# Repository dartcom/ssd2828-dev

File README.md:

# SSD2828-DEV
A collection of boards to test the SSD2828 RGB to MIPI Converter with the LH154Q01 panel by AUO and the VS035ZSM by BOE. The boards are meant to be ordered as a single unit and then be separated using a box cutter ( the dust generated by cutting cutting FR4 is carcenogenic PLEASE be carefull! ).

<br></br>

# The pcb
The pcb is designed using the JLC04161H-7628 stackup by JLCPCB.  The MIPI DSI protool requires controlled impedance traces to function properly (100Ω differental, 50Ω single ended), depending on the provided pcb stackup different trace widths and spacings need to be selected. Additionally the signals must be kept away from noise sources such as inductors and other signals. When switching layers with MIPI signals, GND vias need to be placed near the signal vias.

# LH154Q01 panel
The LH154Q01 panel has been tested and is working correctly.

The panel does not support packed pixel stream packets, the only way to send pixel data to the display, is through DCS commands. in this demo, a STM32f401 is sending the the write_memory_continue(0x3C) DCS command containing pixel data, through SPI to the SSD2828. 

<br></br>

# VS035ZSM panel
The VS035ZSM panel has been tested and is working correctly.

The panel gets initialized on MIPI LP mode and the video is transmitted MIPI HS mode @912Mbps per lane. The ssd2828 is generating the test video signal called BIST. The panel has 8-bit color depth, reaning each pixel requires 24bits. The resolution of the panel is 1400x1600, including the porch values the total resoution is 1470 x 167. To operate at 60fps, 1470 x 1670 x 24 x 60 = 3.53Gbps are required resulting at 883Mbps per lane. The panel also suppors VESA DSC making 90fps operation possible. Unfortunately the SSD2828 does not include a DSC encoder. 

<br></br>

# Resources
### PCB
- [jlcpcb capabilities](https://jlcpcb.com/capabilities/pcb-capabilities).
- [jlcpcb impedance calculator](https://jlcpcb.com/pcb-impedance-calculator).
- [Jacinto 7 High-Speed Interface Layout Guidelines](https://www.ti.com/lit/an/spracp4/spracp4.pdf?ts=1708080453311&ref_url=https%253A%252F%252Fwww.google.com%252F).
- [MIPI DSI guidelines]( https://electronics.stackexchange.com/questions/610671/mipi-dsi-differential-pair-layout-guidance).
- [High-Speed PCB Design Tips - Phil's Lab](https://www.youtube.com/watch?v=VRJI0X-6yTg).
- [Differential Pairs - PCB Design Basics - Phil's Lab](https://www.youtube.com/watch?v=xwrdvhm4vgw).

### SSD2828
- [SSD2828 RGB转MIPI转换板制作（1)](https://blog.csdn.net/weixin_37214729/article/details/123339267).
- [SSD2828 RGB转MIPI转换板制作（2)](https://blog.csdn.net/weixin_37214729/article/details/127710648).
- [SSD2828调试记录](https://blog.csdn.net/luoqindong/article/details/39349333).
- [project-display](https://github.com/jlywxy/project-display).
- [Index of /lcd/ssd2828/](http://www.internetsomething.com/lcd/ssd2828/).

### LH154Q01
- [Driving IPOD Nano 6 MIPI LCD Using FPGA](https://www.circuitvalley.com/2020/01spi-mipi-bridge-fpga-verilog-hdl-ipod-nano-nano-lcd-iphone-mipi-lcd.html).
- [SSD2805 w/ LH154Q01](https://github.com/techtoys/SSD2805/blob/master/Microchip/Graphics/Drivers/SSD2805.c).
### VS035ZSM
- [Project North Star](https://github.com/leapmotion/ProjectNorthStar).

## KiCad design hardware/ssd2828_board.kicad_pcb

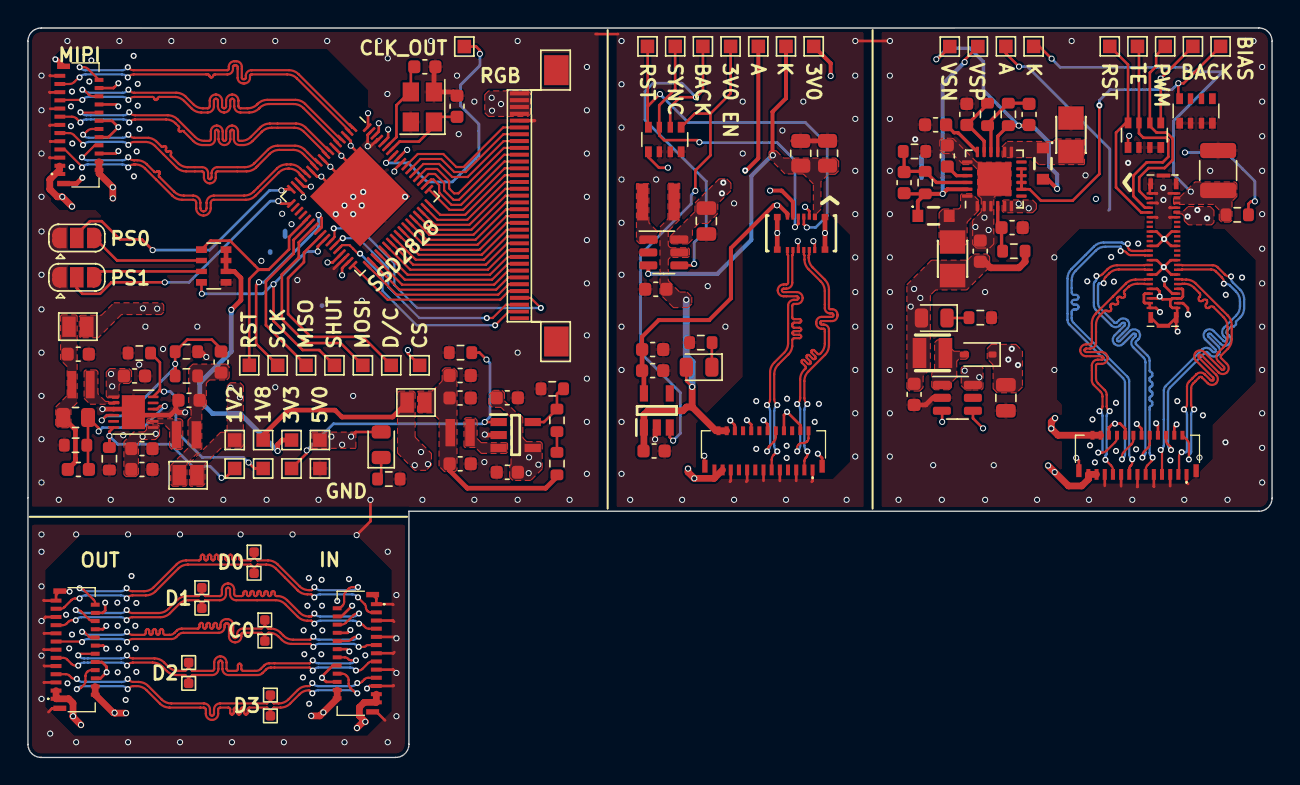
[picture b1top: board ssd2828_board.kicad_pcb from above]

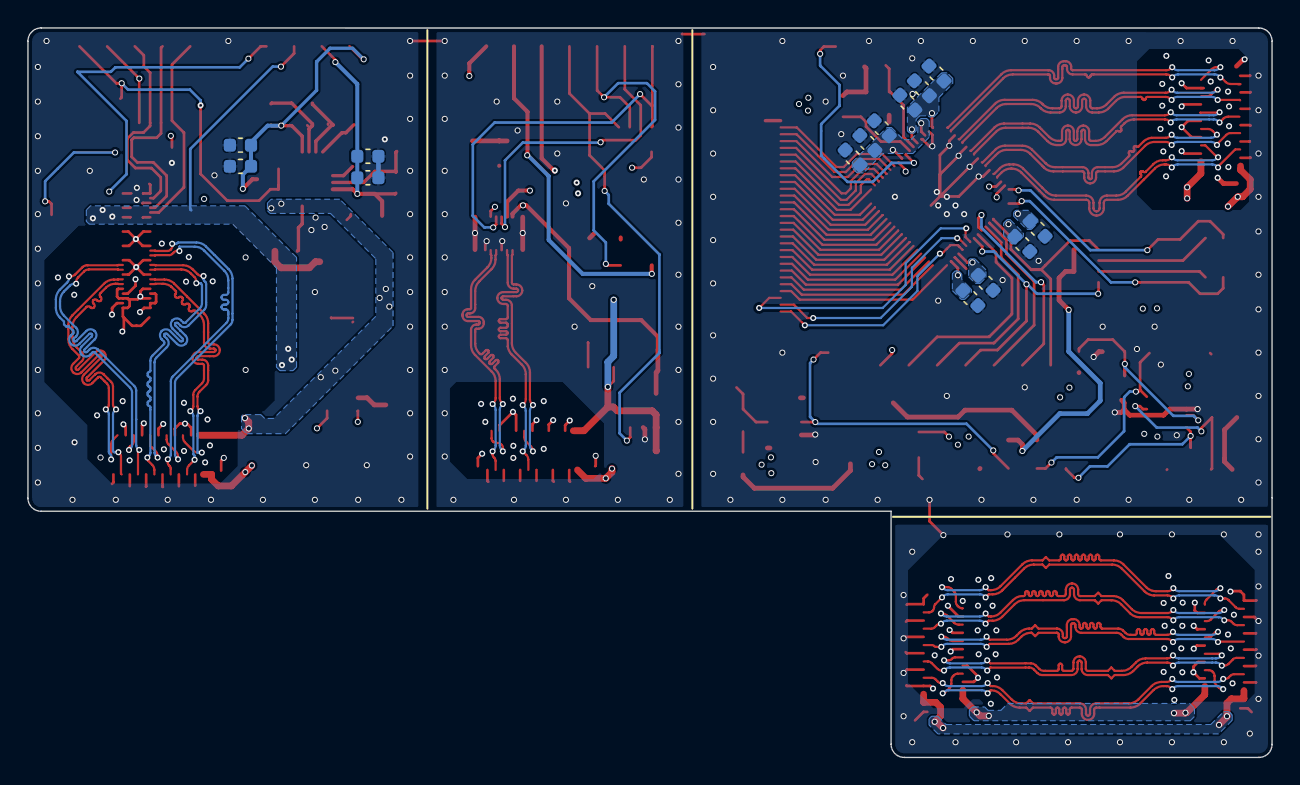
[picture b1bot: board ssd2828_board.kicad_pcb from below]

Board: 4 copper layers, 91.3 x 53.5 mm, 144 parts (14 on the bottom side), 124 nets.

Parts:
C1, C2, C16, C17: 27pf; C_0603_1608Metric
C3, C4, C5, C6, C7, C8, C9, C11, C13, C23, C28: 0.1uf; C_0603_1608Metric
C10, C12, C14, C15, C18, C19, C20, C21, C22, C24, C25, C27, C29, C30, C32, C34, C37, C38, C41: 10uf; C_0603_1608Metric
C26, C42: 2.2uf; C_0805_2012Metric
C31, C36: 1uf; C_0603_1608Metric
C33, C35: 10pf; C_0603_1608Metric
C39: 10nf; C_0603_1608Metric
C40: 4.7nf; C_0603_1608Metric
D1: RB551V-40; D_SOD-323
D2, D3: CUS10S; CUS10S40H3F
D4, D5, D6: LED; LED_0805_2012Metric
IC1: TLV62568DBVR; SOT95P280X145-5N
IC2: MIC5501-3.0YM5-TR; SOT95P280X145-5N
IC3: TPS65131TRGERQ1; VQFN-24-1EP_4x4mm_P0.5mm_EP2.45x2.45mm
J1, J2, J8, J9, J10: FH35C-25S-0.3SHW_50_; FH35C25S03SHW50
J3: Conn_01x34; FPC_34
J4: 245863050104829+; 245863050104829
J5: 503548-1220; 5035481220
JP1, JP2: SolderJumper-3_P1.3mm_Open_RoundedPad1.0x1.5mm
JP3, JP4, JP5: SolderJumper_2_Open; SolderJumper-2_P1.3mm_Open_Pad1.0x1.5mm
L1, L3: 2.2μh; NRH2410T2R2MN
L2: 4.7μh; NRS2012T4R7MGJ
L4: 10uh; ASPI0312FS100MT2
L5, L6: 4.7uh; IND-SMD_L2.5-W2.0_WPN252012H
L7: 4.7uh; IND-SMD_L2.5-W2.0_FHD252012S-6R8MT
R1, R3, R5, R6, R7, R8, R9, R10: 100k; R_0603_1608Metric
R2: 540k; R_0805_2012Metric
R4: 120k; R_0603_1608Metric
R11, R14, R20, R22: 6k8; R_0603_1608Metric
R12: 47r; R_0805_2012Metric
R13: 20r; R_0805_2012Metric
R15: 10r; R_0603_1608Metric
R16: 560k; R_0603_1608Metric
R17, R19: 150k; R_0603_1608Metric
R18: 715k; R_0603_1608Metric
R23: 4r99; R_1210_3225Metric
RN1, RN2, RN3, RN4: 10k; R_Array_Convex_4x0603
TP1, TP2, TP3, TP4, TP5, TP6, TP7, TP8, TP9, TP10, TP11, TP12, TP13, TP14, TP15, TP16, TP17, TP18, TP19, TP20, TP21, TP22, TP23, TP24, TP25, TP26, TP27, TP28, TP29, TP30, TP31, TP42: TestPoint_Pad_1.0x1.0mm
TP32, TP33, TP34, TP35, TP36, TP37, TP38, TP39, TP40, TP41: myTestpoint
U1: SSD2828QN4; QFN-68-1EP_8x8mm_P0.4mm_EP5.2x5.2mm
U2: PAM2306DYPAA; WDFN-12-1EP_3x3mm_P0.45mm_EP1.7x2.5mm
U3: MIC3289; SOT-23-6
U4: LP3320; SOT-23-6
Y1: 24mhz; Crystal_SMD_3225-4Pin_3.2x2.5mm

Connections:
+1V2: C3.1, C4.1, C6.1, C8.1, C10.1, JP5.2 (B), TP5.1, U1.15 (MVDD), U1.31 (MVDD), U1.60 (MVDD), U1.66 (MVDD)
+1V8: J1.1, J1.3, J2.23, J2.25, J4.2, J4.4, J4.8, J5.4, J8.23, J8.25, J9.23, J9.25, J10.1, J10.3, JP3.2 (B), RN2.1 (R1.1), RN3.1 (R1.1), TP7.1
+3V0: C28.1, C29.1, IC2.5 (VOUT), J5.2, TP13.1
+3V3: C5.1, C7.1, C9.1, C11.1, C12.1, JP4.2 (B), RN1.6 (R3.2), RN1.7 (R2.2), RN1.8 (R1.2), TP6.1, U1.16 (VDDIO), U1.33 (VDDIO), U1.64 (VDDIO), U1.68 (VDDIO)
+5V: C13.1, C14.1, C15.1, C23.1, C24.1, C25.1, C27.2, C30.1, C41.2, D4.2 (A), D5.2 (A), D6.2 (A), IC1.4 (VIN), IC2.1 (VIN), IC3.5 (INN_1), IC3.6 (INN_2), J1.2, J1.4, J2.22, J2.24, J3.31, J3.32, J3.33, J3.34, J8.22, J8.24, J9.22, J9.24, J10.2, J10.4, L4.1, L5.1, L7.1, R15.2, TP3.1, U2.1 (VIN2), U2.7 (VIN1), U3.5 (VIN), U4.6 (VIN)
/LH154Q01/3V0_EN: IC2.3 (EN), RN2.5 (R4.2), TP15.1
/LH154Q01/BACKLIGHT_EN: RN2.6 (R3.2), TP14.1, U3.4 (DC)
/LH154Q01/B_Sync: J5.6, RN2.7 (R2.2), TP9.1
/LH154Q01/LED_A: C26.1, J5.10, TP16.1, U3.6 (OUT)
/LH154Q01/LED_K: J5.12, R12.2, R13.2, TP29.1, U3.3 (FB)
/LH154Q01/MIPI_CLK_N: J5.3, J8.11
/LH154Q01/MIPI_CLK_P: J5.1, J8.10
/LH154Q01/MIPI_DATA0_N: J5.9, J8.3
/LH154Q01/MIPI_DATA0_P: J5.7, J8.2
/LH154Q01/RST: J5.8, RN2.8 (R1.2), TP8.1
/SSD2828/1V2_EN: R6.1, TP11.1, U2.6 (EN1)
/SSD2828/1V8_EN: IC1.1 (EN), R10.1, TP12.1
/SSD2828/3V3_EN: R5.1, TP10.1, U2.12 (EN2)
/SSD2828/CLK_XIN: C2.2, U1.63 (TX_CLK_XIN), Y1.3
/SSD2828/CLK_XIO: C1.2, U1.62 (TX_CLK_XIO), Y1.1
/SSD2828/CS: TP20.1, U1.59 (CSX0)
/SSD2828/D/C: TP19.1, U1.26 (SDC)
/SSD2828/MIPI_CLK_N: J1.15, U1.8 (CLKN)
/SSD2828/MIPI_CLK_P: J1.16, U1.7 (CLKP)
/SSD2828/MIPI_DATA0_N: J1.23, U1.2 (DATAN0)
/SSD2828/MIPI_DATA0_P: J1.24, U1.1 (DATAP0)
/SSD2828/MIPI_DATA1_N: J1.19, U1.5 (DATAN1)
/SSD2828/MIPI_DATA1_P: J1.20, U1.4 (DATAP1)
/SSD2828/MIPI_DATA2_N: J1.11, U1.11 (DATAN2)
/SSD2828/MIPI_DATA2_P: J1.12, U1.10 (DATAP2)
/SSD2828/MIPI_DATA3_N: J1.7, U1.14 (DATAN3)
/SSD2828/MIPI_DATA3_P: J1.8, U1.13 (DATAP3)
/SSD2828/MISO: TP17.1, U1.23 (SDO)
/SSD2828/MOSI: TP4.1, U1.24 (SDI)
/SSD2828/PS0: JP1.2 (C), U1.17 (PS0)
/SSD2828/PS1: JP2.2 (C), U1.18 (PS1)
/SSD2828/RESET: RN1.1 (R1.1), TP1.1, U1.22 (RESET)
/SSD2828/RGB_B0: J3.6, U1.35 (DATA0)
/SSD2828/RGB_B1: J3.7, U1.36 (DATA1)
/SSD2828/RGB_B2: J3.8, U1.37 (DATA2)
/SSD2828/RGB_B3: J3.9, U1.38 (DATA3)
/SSD2828/RGB_B4: J3.10, U1.39 (DATA4)
/SSD2828/RGB_B5: J3.11, U1.40 (DATA5)
/SSD2828/RGB_B6: J3.12, U1.41 (DATA6)
/SSD2828/RGB_B7: J3.13, U1.42 (DATA7)
/SSD2828/RGB_CLK: J3.2, U1.30 (PCLK)
/SSD2828/RGB_EN: J3.4, U1.28 (DEN)
/SSD2828/RGB_G0: J3.14, U1.43 (DATA8)
/SSD2828/RGB_G1: J3.15, U1.44 (DATA9)
/SSD2828/RGB_G2: J3.16, U1.45 (DATA10)
/SSD2828/RGB_G3: J3.17, U1.46 (DATA11)
/SSD2828/RGB_G4: J3.18, U1.47 (DATA12)
/SSD2828/RGB_G5: J3.19, U1.48 (DATA13)
/SSD2828/RGB_G6: J3.20, U1.49 (DATA14)
/SSD2828/RGB_G7: J3.21, U1.50 (DATA15)
/SSD2828/RGB_HSYNC: J3.3, U1.29 (HSYNC)
/SSD2828/RGB_R0: J3.22, U1.51 (DATA16)
/SSD2828/RGB_R1: J3.23, U1.52 (DATA17)
/SSD2828/RGB_R2: J3.24, U1.53 (DATA18)
/SSD2828/RGB_R3: J3.25, U1.54 (DATA19)
/SSD2828/RGB_R4: J3.26, U1.55 (DATA20)
/SSD2828/RGB_R5: J3.27, U1.56 (DATA21)
/SSD2828/RGB_R6: J3.28, U1.57 (DATA22)
/SSD2828/RGB_R7: J3.29, U1.58 (DATA23)
/SSD2828/RGB_VSYNC: J3.5, U1.34 (VSYNC)
/SSD2828/SCK: TP18.1, U1.25 (SCK)
/SSD2828/SHUT: RN1.4 (R4.1), TP2.1, U1.27 (SHUT)
/VS035ZSM/BACKLIGHT_EN: RN3.5 (R4.2), TP23.1, U4.4 (EN)
/VS035ZSM/BIAS_EN: IC3.8 (ENP), IC3.9 (PSP), IC3.10 (ENN), IC3.11 (PSN), RN4.8 (R1.2), TP22.1
/VS035ZSM/LED_A: C42.1, D1.1 (K), J4.41, TP24.1
/VS035ZSM/LED_K_1: J4.45, J4.47, R22.2, R23.1, TP27.1
/VS035ZSM/LED_PWM: J4.48, RN3.6 (R3.2), TP28.1
/VS035ZSM/MIPI_CLK_N: J2.11, J4.18
/VS035ZSM/MIPI_CLK_P: J2.10, J4.20
/VS035ZSM/MIPI_DATA0_N: J2.3, J4.11
/VS035ZSM/MIPI_DATA0_P: J2.2, J4.13
/VS035ZSM/MIPI_DATA1_N: J2.7, J4.17
/VS035ZSM/MIPI_DATA1_P: J2.6, J4.19
/VS035ZSM/MIPI_DATA2_N: J2.15, J4.24
/VS035ZSM/MIPI_DATA2_P: J2.14, J4.26
/VS035ZSM/MIPI_DATA3_N: J2.19, J4.12
/VS035ZSM/MIPI_DATA3_P: J2.18, J4.14
/VS035ZSM/RST: J4.42, RN3.8 (R1.2), TP25.1
/VS035ZSM/TE: J4.44, RN3.7 (R2.2), TP26.1
/VS035ZSM/VSN: C35.2, C37.1, C38.1, D2.2 (A), IC3.15 (VNEG), J4.7, R18.2, TP31.1
/VS035ZSM/VSP: C32.1, C33.2, C34.1, D3.1 (K), IC3.23 (VPOS), J4.3, R16.2, TP30.1
/debug/MIPI_CLK_N: J9.11, J10.15, TP37.1
/debug/MIPI_CLK_P: J9.10, J10.16, TP36.1
/debug/MIPI_DATA0_N: J9.3, J10.23, TP33.1
/debug/MIPI_DATA0_P: J9.2, J10.24, TP32.1
/debug/MIPI_DATA1_N: J9.7, J10.19, TP35.1
/debug/MIPI_DATA1_P: J9.6, J10.20, TP34.1
/debug/MIPI_DATA2_N: J9.15, J10.11, TP39.1
/debug/MIPI_DATA2_P: J9.14, J10.12, TP38.1
/debug/MIPI_DATA3_N: J9.19, J10.7, TP41.1
/debug/MIPI_DATA3_P: J9.18, J10.8, TP40.1
GND: C1.1, C2.1, C3.2, C4.2, C5.2, C6.2, C7.2, C8.2, C9.2, C10.2, C11.2, C12.2, C13.2, C14.2, C15.2, C18.2, C19.2, C20.2, C21.2, C22.2, C23.2, C24.2, C25.2, C26.2, C27.1, C28.2, C29.2, C30.2, C31.2, C32.2, C34.2, C36.2, C37.2, C38.2, C39.2, C40.2, C41.1, C42.2, IC1.2 (GND), IC2.2 (GND), IC3.2 (PGND_1), IC3.3 (PGND_2), IC3.19 (AGND), IC3.25 (EP), J1.5, J1.6, J1.9, J1.10, J1.13, J1.14, J1.17, J1.18, J1.21, J1.22, J1.25, J1.MP1, J1.MP2, J2.1, J2.4, J2.5, J2.8, J2.9, J2.12, J2.13, J2.16, J2.17, J2.20, J2.21, J2.MP1, J2.MP2, J3.1, J3.30, J4.1, J4.5, J4.6, J4.9, J4.10, J4.15, J4.16, J4.21, J4.22, J4.27, J4.28, J4.33, J4.34, J4.39, J4.40, J4.43, J4.46, J4.49, J4.50, J4.MP1, J4.MP2, J4.MP3, J4.MP4, J4.MP5, J4.MP6, J5.5, J5.11, J5.MP1, J5.MP2, J5.MP3, J5.MP4, J8.1, J8.4, J8.5, J8.8, J8.9, J8.12, J8.13, J8.16, J8.17, J8.20, J8.21, J8.MP1, J8.MP2, J9.1, J9.4, J9.5, J9.8, J9.9, J9.12, J9.13, J9.16, J9.17, J9.20, J9.21, J9.MP1, J9.MP2, J10.5, J10.6, J10.9, J10.10, J10.13, J10.14, J10.17, J10.18, J10.21, J10.22, J10.25, J10.MP1, J10.MP2, JP1.1 (A), JP2.1 (A), L6.1, R3.2, R4.2, R5.2, R6.2, R9.2, R10.2, R11.1, R12.1, R13.1, R14.1, R17.2, R20.1, R23.2, RN1.5 (R4.2), RN2.2 (R2.1), RN2.3 (R3.1), RN2.4 (R4.1), RN3.2 (R2.1), RN3.3 (R3.1), RN3.4 (R4.1), RN4.1 (R1.1), RN4.2 (R2.1), RN4.3 (R3.1), RN4.4 (R4.1), TP21.1, U1.3 (GND), U1.6 (GND), U1.9 (GND), U1.12 (GND), U1.32 (GND), U1.65 (GND), U1.67 (GND), U1.69 (GND), U2.3 (GND), U2.9 (GND), U2.13 (GND), U3.2 (GND), U4.2 (GND), Y1.2, Y1.4
unnamed: D1.2 (A), L7.2, U4.1 (SW)
unnamed: D2.1 (K), IC3.13 (OUTN), IC3.14 (OUT_N), L6.2
unnamed: D3.2 (A), IC3.1 (INP_1), IC3.24 (INP_2), L5.2
unnamed: D4.1 (K), R11.2
unnamed: D5.1 (K), R14.2
unnamed: D6.1 (K), R20.2
unnamed: IC1.5 (FB), R7.2, R9.1
unnamed: IC1.3 (SW), L3.1
unnamed: C40.1, IC3.18 (CN)
unnamed: C39.1, IC3.21 (CP)
unnamed: C35.1, IC3.16 (FBN), R18.1, R19.1
unnamed: C33.1, IC3.22 (FBP), R16.1, R17.1
unnamed: C31.1, IC3.4 (VIN), R15.1
unnamed: C36.1, IC3.17 (VREF), R19.2
unnamed: JP1.3 (B), RN1.2 (R2.1)
unnamed: JP2.3 (B), RN1.3 (R3.1)
unnamed: C20.1, C21.1, C22.1, JP3.1 (A), L3.2, R8.1
unnamed: C17.1, C19.1, JP4.1 (A), L2.2, R2.1
unnamed: C16.1, C18.1, JP5.1 (A), L1.2, R1.1
unnamed: R7.1, R8.2
unnamed: TP42.1, U1.61 (SYS_CLK_OUT)
unnamed: C16.2, R1.2, R3.1, U2.4 (FB1)
unnamed: C17.2, R2.2, R4.1, U2.10 (FB2)
unnamed: L1.1, U2.8 (LX1)
unnamed: L2.1, U2.2 (LX2)
unnamed: L4.2, U3.1 (SW)
unnamed: R22.1, U4.3 (FB)

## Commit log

2023-07-06 commiting schemtics.pdf
2023-07-12 fixed some intra-pair skew errors and filleted some lanes
2023-07-12 added separations for each board on the copper fills
2023-07-15 tweaked some MIPI traces on the SSD2828 board
2023-07-16 added solder bridges on all the generated voltage rails on the SSD2828 board
2023-07-17 updated tps6513 footprint to vqfn24 + fixed some missing connections near it
2023-07-27 changed the order of pins on the rgb connector + removed a pin from the schematic symbol
2023-08-14 retouched copper fills + started reordering the power nets
2023-08-26 fixing drc errors + adding debug board for mipi
2023-09-14 routed 1v2 to ssd2828 + finished debug board
2023-09-25 finished with vias + fixed board outlines
2023-09-27 making the project portableby moving external libaries to the project
2023-10-01 updated 3d models to the correct paths for kicad 7 + added HTML interactive BOM
2023-10-15 added via stitching and updated the bias generator layout
2023-10-15 removed backups
2023-11-02 fixed details
2023-11-02 fixed some 3d models + redid power distribution on the BOE board
2023-11-02 added fresh gerbers
2023-11-02 version 1.0
2023-11-16 added copper pour on back layer to adhere with jlcpcb guidelines
2023-11-30 fixed hirose FPC connector poinitng backwards on the 2 lcd boards+added stm32f401 boilerplate code
2023-11-30 changed gitignore to include the software/build folder
2023-11-30 length tuned mipi lines on ssd2828 board
2023-12-01 added config for cortex debug + added blink for stm32
2023-12-01 added configs
2023-12-03 added clock configuration + systick delay
2023-12-04 the internal id of the ssd2828 can be read
2023-12-04 started on the ssd28282 library
2023-12-05 continuing on the ssd2828 register definitions
2023-12-08 finished register definitions, need to look at functions
2023-12-12 updated Ibom and wrote some code
2023-12-12 progress with init code
2023-12-18 backup
2023-12-20 small screen works
2024-02-03 working code
2024-02-03 working code 2
2024-02-03 updated readme + fixed pcb + cleaned up code
2024-02-04 started on the code for the BOE panel + fixed VSN VSP labels on PCB
2024-02-07 BOE panel working
2024-02-07 data can be transmitted @912Mbps
2024-12-15 fixed kicad performance issues with GND plane
